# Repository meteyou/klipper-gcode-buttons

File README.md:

# Klipper Gcode-Buttons

The Klipper Gcode-Buttons offer a unique control and status display solution in 3D printers and automated systems.
Executing gcodes directly via hardware buttons and displaying the status visually significantly increases
user-friendliness. The CANBUS support as a USB-to-CAN adapter and the additional interfaces, such as SPI and I2C, offer
extra benefits and significantly expand the application possibilities.

To learn more about the Klipper Gcode-Buttons, check out the documentation:
[Klipper Gcode-Buttons Documentation](https://gcode-buttons.meteyou.wtf)

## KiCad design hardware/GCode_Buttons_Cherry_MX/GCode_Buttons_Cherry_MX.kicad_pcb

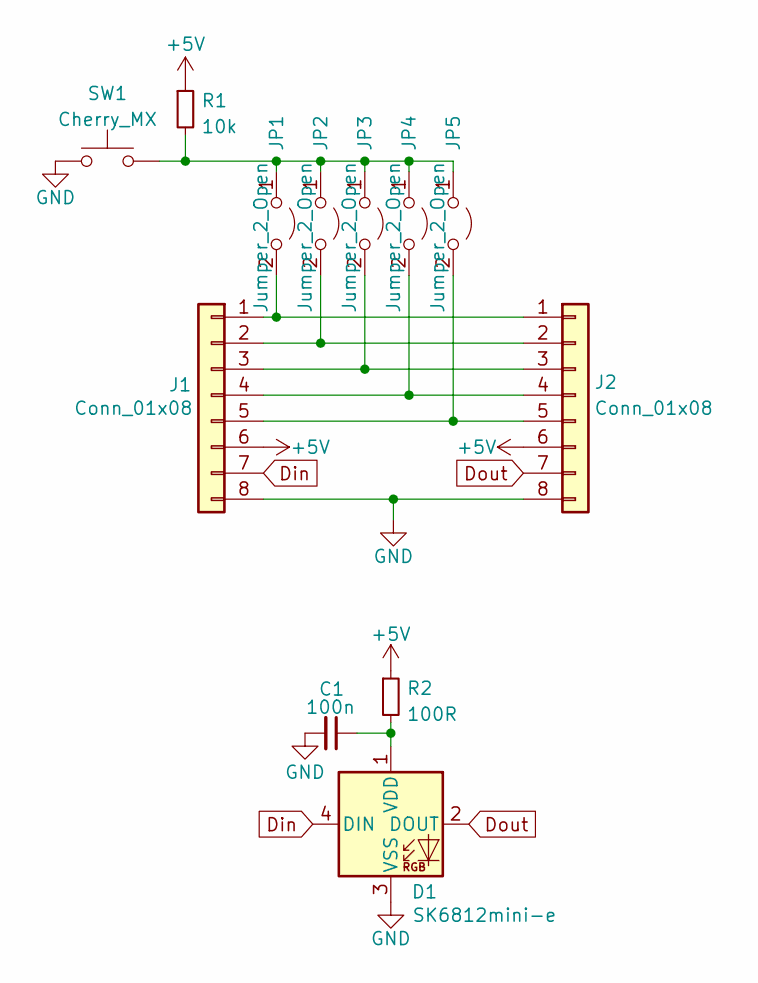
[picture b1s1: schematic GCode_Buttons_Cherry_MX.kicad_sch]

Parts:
C1: 100n; C_0402_1005Metric; LCSC C60474
D1: SK6812mini-e; SK6812MINI-E; LCSC C784561
J1, J2: Conn_01x08; JUSHUO AFC11-S08ICC-00; LCSC C262301
JP1, JP2, JP3, JP4, JP5: Jumper_2_Open; SolderJumper-2_P1.3mm_Open_Pad1.0x1.5mm
R1: 10k; R_0402_1005Metric; LCSC C144807
R2: 100R; R_0402_1005Metric; LCSC C25076
SW1: Cherry_MX; SW_Cherry_MX_1.00u_PCB

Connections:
+5V: J1.6, J2.6, R1.1, R2.1
Din: D1.4 (DIN), J1.7
Dout: D1.2 (DOUT), J2.7
GND: C1.2, D1.3 (VSS), J1.8, J2.8, SW1.2
unnamed: C1.1, D1.1 (VDD), R2.2
unnamed: J1.1, J2.1, JP1.2 (B)
unnamed: J1.2, J2.2, JP2.2 (B)
unnamed: J1.3, J2.3, JP3.2 (B)
unnamed: J1.4, J2.4, JP4.2 (B)
unnamed: J1.5, J2.5, JP5.2 (B)
unnamed: JP1.1 (A), JP2.1 (A), JP3.1 (A), JP4.1 (A), JP5.1 (A), R1.2, SW1.1

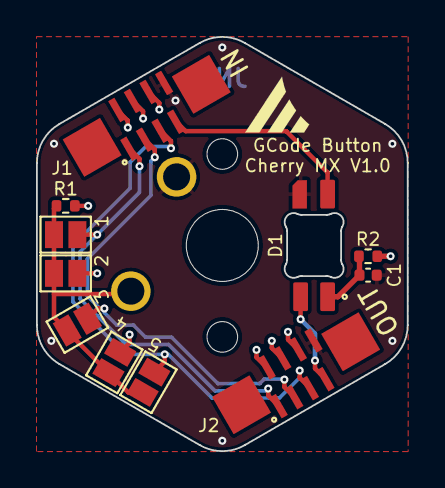
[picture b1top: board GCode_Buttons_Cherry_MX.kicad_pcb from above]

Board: 4 copper layers, 20.6 x 23.0 mm, 12 parts (1 on the bottom side), 11 nets.

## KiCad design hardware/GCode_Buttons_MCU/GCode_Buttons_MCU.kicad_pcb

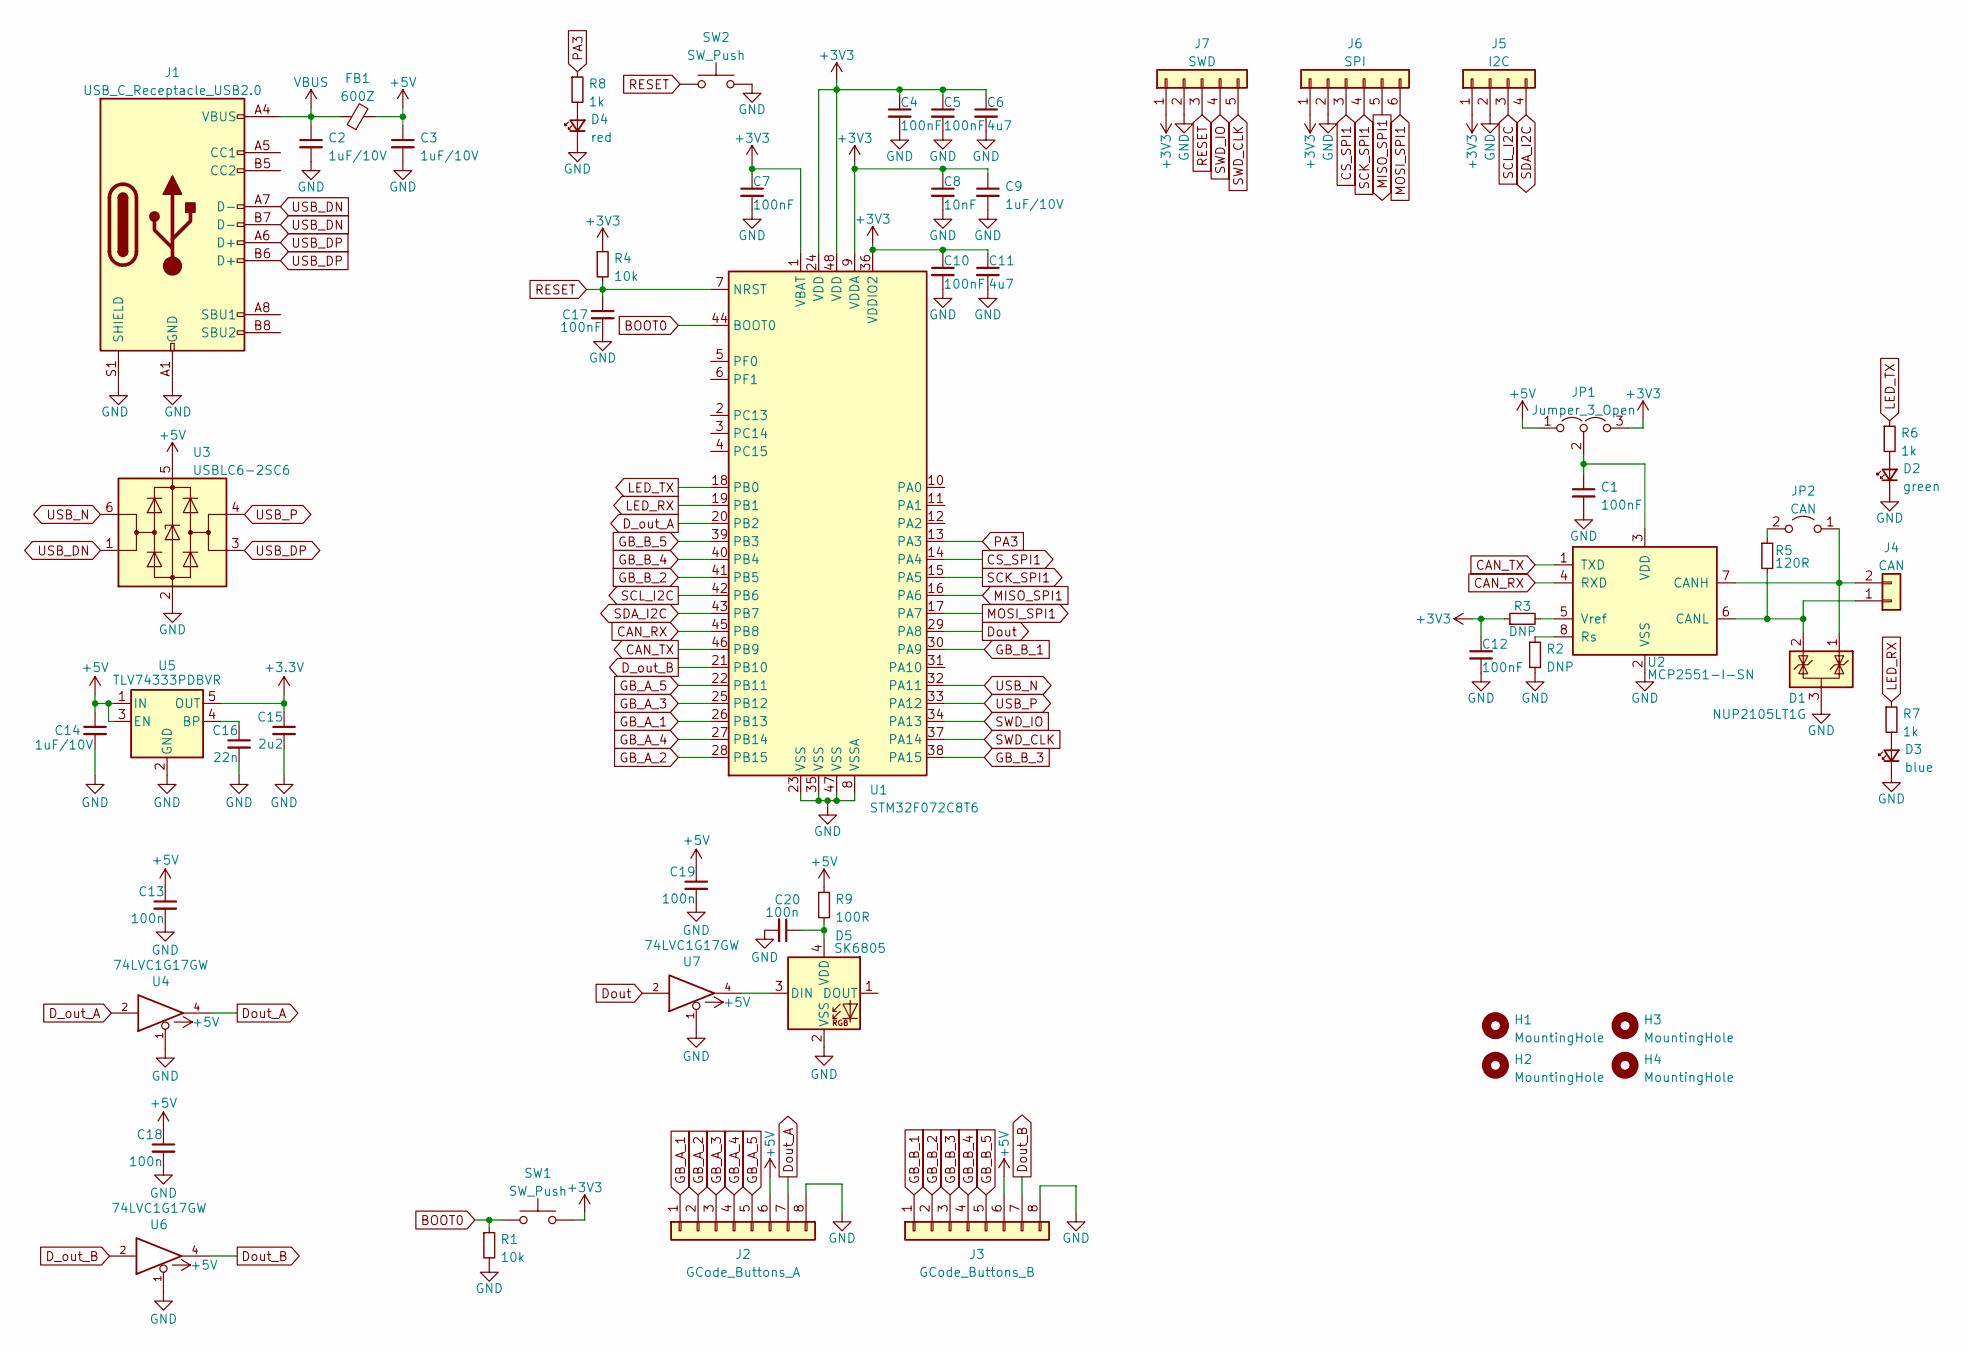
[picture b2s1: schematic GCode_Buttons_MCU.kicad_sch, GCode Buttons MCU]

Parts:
C1, C4, C5, C7, C10, C12, C17: 100nF; C_0402_1005Metric; LCSC C60474
C2, C3, C9, C14: 1uF/10V; C_0402_1005Metric; LCSC C528974
C6, C11: 4u7; C_0402_1005Metric; LCSC C368809
C8: 10nF; C_0402_1005Metric; LCSC C327025
C13, C18, C19, C20: 100n; C_0402_1005Metric; LCSC C60474
C15: 2u2; C_0402_1005Metric; LCSC C415540
C16: 22n; C_0402_1005Metric; LCSC C107026
D1: NUP2105LT1G; SOT-23; LCSC C2976509
D2: green; LED_0402_1005Metric; LCSC C401111
D3: blue; LED_0402_1005Metric; LCSC C401112
D4: red; LED_0402_1005Metric; LCSC C71911
D5: SK6805; LED_SK6805_PLCC4_2.4x2.7mm_P1.3mm; LCSC C784561
FB1: 600Z; L_0603_1608Metric; LCSC C19330
H1, H2, H3, H4: MountingHole; MountingHole_2.2mm_M2_DIN965
J1: USB_C_Receptacle_USB2.0; USB_C_Receptacle_HRO_TYPE-C-31-M-12; LCSC C136423
J2: GCode_Buttons_A; JUSHUO AFC11-S08ICC-00; LCSC C262301
J3: GCode_Buttons_B; JUSHUO AFC11-S08ICC-00; LCSC C262301
J4: CAN; JST_XH_B2B-XH-A_1x02_P2.50mm_Vertical; LCSC C265283
J5: I2C; JST_SH_BM04B-SRSS-TB_1x04-1MP_P1.00mm_Vertical; LCSC C145961
J6: SPI; JST_SH_BM06B-SRSS-TB_1x06-1MP_P1.00mm_Vertical; LCSC C145963
J7: SWD; JST_SH_BM05B-SRSS-TB_1x05-1MP_P1.00mm_Vertical; LCSC C3041143
JP1: Jumper_3_Open; SolderJumper-3_P1.3mm_Open_RoundedPad1.0x1.5mm_NumberLabels
JP2: CAN; PinHeader_1x02_P2.54mm_Vertical; LCSC C492401
R1, R4: 10k; R_0402_1005Metric; LCSC C144807
R2, R3: DNP; R_0402_1005Metric
R5: 120R; R_0402_1005Metric; LCSC C25079
R6, R7, R8: 1k; R_0402_1005Metric; LCSC C144789
R9: 100R; R_0402_1005Metric; LCSC C25076
SW1, SW2: SW_Push; SW_SPST_1TS003B-1400-3500A-CT; LCSC C319392
U1: STM32F072C8T6; LQFP-48_7x7mm_P0.5mm; LCSC C80488
U2: MCP2551-I-SN; SOIC-8_3.9x4.9mm_P1.27mm; LCSC C7376
U3: USBLC6-2SC6; SOT-23-6; LCSC C7519
U4, U6, U7: 74LVC1G17GW; SOT-353_SC-70-5; LCSC C202202
U5: TLV74333PDBVR; SOT-23-5; LCSC C408972

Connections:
+5V: C3.1, C13.1, C14.1, C18.1, C19.1, FB1.2, J2.6, J3.6, JP1.1 (A), R9.1, U3.5 (VBUS), U4.5 (VCC), U5.1 (IN), U5.3 (EN), U6.5 (VCC), U7.5 (VCC)
BOOT0: R1.1, SW1.1, U1.44 (BOOT0)
CAN_RX: U1.45 (PB8), U2.4 (RXD)
CAN_TX: U1.46 (PB9), U2.1 (TXD)
CS_SPI1: J6.3, U1.14 (PA4)
D_out_A: U1.20 (PB2), U4.2
D_out_B: U1.21 (PB10), U6.2
Dout: U1.29 (PA8), U7.2
Dout_A: J2.7, U4.4
Dout_B: J3.7, U6.4
GB_A_1: J2.1, U1.26 (PB13)
GB_A_2: J2.2, U1.28 (PB15)
GB_A_3: J2.3, U1.25 (PB12)
GB_A_4: J2.4, U1.27 (PB14)
GB_A_5: J2.5, U1.22 (PB11)
GB_B_1: J3.1, U1.30 (PA9)
GB_B_2: J3.2, U1.41 (PB5)
GB_B_3: J3.3, U1.38 (PA15)
GB_B_4: J3.4, U1.40 (PB4)
GB_B_5: J3.5, U1.39 (PB3)
GND: C1.2, C2.2, C3.2, C4.2, C5.2, C6.2, C7.2, C8.2, C9.2, C10.2, C11.2, C12.2, C13.2, C14.2, C15.2, C16.2, C17.2, C18.2, C19.2, C20.2, D1.3 (A), D2.1 (K), D3.1 (K), D4.1 (K), D5.2 (VSS), J1.A1 (GND), J1.A12 (GND), J1.B1 (GND), J1.B12 (GND), J1.S1 (SHIELD), J2.8, J3.8, J5.2, J6.2, J7.2, R1.2, R2.2, SW2.1, U1.8 (VSSA), U1.23 (VSS), U1.35 (VSS), U1.47 (VSS), U2.2 (VSS), U3.2 (GND), U4.1, U4.3 (GND), U5.2 (GND), U6.1, U6.3 (GND), U7.1, U7.3 (GND)
LED_RX: R7.1, U1.19 (PB1)
LED_TX: R6.1, U1.18 (PB0)
MISO_SPI1: J6.5, U1.16 (PA6)
MOSI_SPI1: J6.6, U1.17 (PA7)
unnamed: C1.1, JP1.2 (C), U2.3 (VDD)
unnamed: C16.1, U5.4 (BP)
unnamed: C20.1, D5.4 (VDD), R9.2
unnamed: D1.1 (K), J4.2, JP2.1 (A), U2.7 (CANH)
unnamed: D1.2 (K), J4.1, R5.2, U2.6 (CANL)
unnamed: D2.2 (A), R6.2
unnamed: D3.2 (A), R7.2
unnamed: D4.2 (A), R8.2
unnamed: D5.3 (DIN), U7.4
unnamed: JP2.2 (B), R5.1
unnamed: R2.1, U2.8 (Rs)
unnamed: R3.2, U2.5 (Vref)
PA3: R8.1, U1.13 (PA3)
RESET: C17.1, J7.3, R4.2, SW2.2, U1.7 (NRST)
SCK_SPI1: J6.4, U1.15 (PA5)
SCL_I2C: J5.3, U1.42 (PB6)
SDA_I2C: J5.4, U1.43 (PB7)
SWD_CLK: J7.5, U1.37 (PA14)
SWD_IO: J7.4, U1.34 (PA13)
USB_DN: J1.A7 (D-), J1.B7 (D-), U3.1 (I/O1)
USB_DP: J1.A6 (D+), J1.B6 (D+), U3.3 (I/O2)
USB_N: U1.32 (PA11), U3.6 (I/O1)
USB_P: U1.33 (PA12), U3.4 (I/O2)
VBUS: C2.1, FB1.1, J1.A4 (VBUS), J1.A9 (VBUS), J1.B4 (VBUS), J1.B9 (VBUS)

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
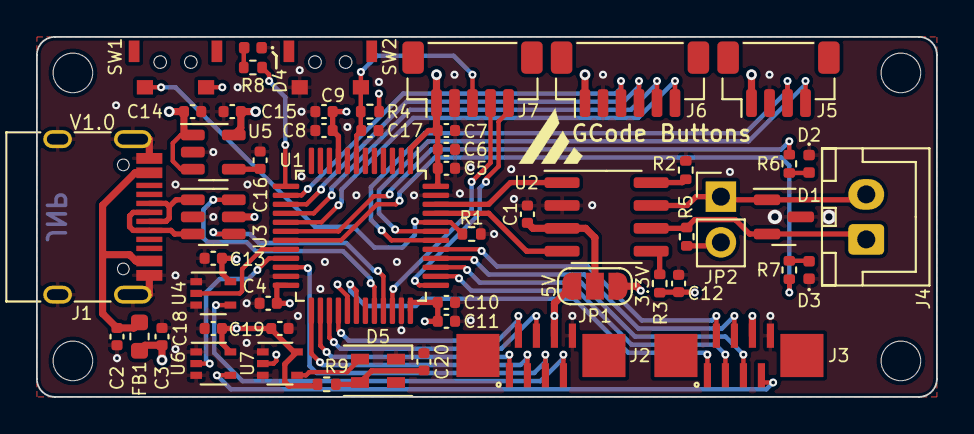
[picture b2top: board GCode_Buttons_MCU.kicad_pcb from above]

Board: 4 copper layers, 50.0 x 20.0 mm, 57 parts (0 on the bottom side), 50 nets.

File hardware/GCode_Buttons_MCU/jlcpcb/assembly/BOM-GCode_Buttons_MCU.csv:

Comment,Designator,Footprint,LCSC
22n,C16,C_0402_1005Metric,C107026
USB_C_Receptacle_USB2.0,J1,USB_C_Receptacle_HRO_TYPE-C-31-M-12,C136423
1k,"R6,R7,R8",R_0402_1005Metric,C144789
10k,"R1,R4",R_0402_1005Metric,C144807
I2C,J5,JST_SH_BM04B-SRSS-TB_1x04-1MP_P1.00mm_Vertical,C145961
600Z,FB1,L_0603_1608Metric,C19330
74LVC1G17GW,"U4,U6,U7",SOT-353_SC-70-5,C202202
100R,R9,R_0402_1005Metric,C25076
120R,R5,R_0402_1005Metric,C25079
GCode_Buttons_A,"J2,J3",JUSHUO AFC11-S08ICC-00,C262301
B2B-XH-A-GU,J4,JST_XH_B2B-XH-A_1x02_P2.50mm_Vertical,C265283
NUP2105LT1G,D1,SOT-23,C2976509
SWD,J7,C145962,C145962
SPI,J6,C145963,C145963
SW_Push,"SW1,SW2",SW_SPST_1TS003B-1400-3500A-CT,C319392
10nF,C8,C_0402_1005Metric,C327025
4u7,"C11,C6",C_0402_1005Metric,C368809
TLV74333PDBVR,U5,SOT-23-5,C408972
2u2,C15,C_0402_1005Metric,C415540
MHT136UBCT,D3,LED_0402_1005Metric,C401112
MHT136CGCT,D2,LED_0402_1005Metric,C401111
CAN,JP2,PinHeader_1x02_P2.54mm_Vertical,C492401
1uF/10V,"C14,C2,C3,C9",C_0402_1005Metric,C528974
100nF,"C1,C10,C12,C13,C17,C18,C19,C20,C4,C5,C7",C_0402_1005Metric,C60474
red,D4,LED_0402_1005Metric,C71911
MCP2551-I-SN,U2,SOIC-8_3.9x4.9mm_P1.27mm,C7376
USBLC6-2SC6,U3,SOT-23-6,C7519
SK6805,D5,LED_SK6805_PLCC4_2.4x2.7mm_P1.3mm,C784561
STM32F072C8T6,U1,LQFP-48_7x7mm_P0.5mm,C80488

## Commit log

2024-08-11 docs: initial upload from mkdocs
2024-08-11 chore: initial upload from gitignore
2024-08-11 docs: set some basic settings for mkdocs
2024-08-11 chore: add .cache to gitignore
2024-08-11 ci: add build ci workflow
2024-08-11 Create CNAME
2024-08-11 docs: init index.md description from the gcode-buttons
2024-08-11 docs: fix typo in the index.md
2024-08-11 docs: add short description + link to the docs in README.md
2024-08-12 docs: disable toc on index.md
2024-08-12 feat: upload Communication Board files
2024-08-12 feat: upload CAD files for MCU case
2024-08-12 feat: upload STLs for MCU case
2024-08-12 feat: upload pinout for Communication Board
2024-08-12 chore: add markdown extension for blank target links
2024-08-12 docs: add the communication board page + images
2024-08-12 feat: upload Romer-G hardware files
2024-08-12 feat: upload Cherry-MX hardware files
2024-08-12 docs: add page for the button boards
2024-08-12 Deployed 86fe06f with MkDocs version: 1.6.0
